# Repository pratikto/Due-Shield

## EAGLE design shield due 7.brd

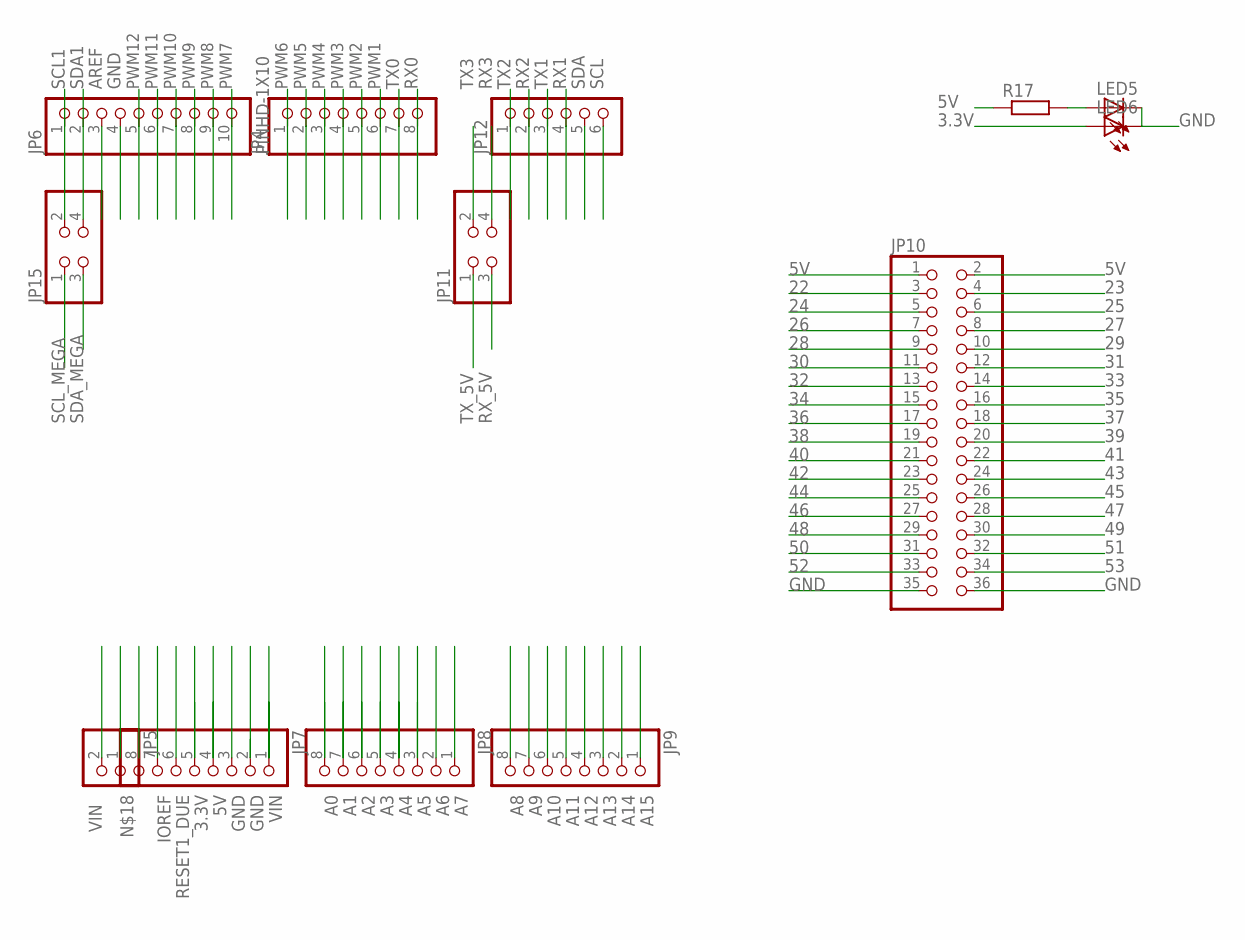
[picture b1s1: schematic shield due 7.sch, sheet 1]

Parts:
JP4, JP7: PINHD-1X8; 1X08
JP5: PINHD-1X2; 1X02
JP6: PINHD-1X10; 1X10-BIG
JP8, JP9: PINHD-1X8BIG; 1X08-BIG
JP10: PINHD-2X18; 2X18
JP11, JP15: PINHD-2X2; 2X02
JP12: PINHD-1X6; 1X06
LED5, LED6: LEDCHIPLED_0805; CHIPLED_0805
R17: R-EU_R0805W; R0805W

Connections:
3.3V: JP7.5, LED6.A; also elsewhere on the board
5V: JP7.4, JP10.1, JP10.2, R17.1; also elsewhere on the board
22: JP10.3
23: JP10.4
24: JP10.5
25: JP10.6
26: JP10.7
27: JP10.8
28: JP10.9
29: JP10.10
30: JP10.11
31: JP10.12
32: JP10.13
33: JP10.14
34: JP10.15
35: JP10.16; also elsewhere on the board
36: JP10.17; also elsewhere on the board
37: JP10.18; also elsewhere on the board
38: JP10.19; also elsewhere on the board
39: JP10.20; also elsewhere on the board
40: JP10.21; also elsewhere on the board
41: JP10.22
42: JP10.23
43: JP10.24
44: JP10.25
45: JP10.26
46: JP10.27
47: JP10.28
48: JP10.29
49: JP10.30
50: JP10.31
51: JP10.32
52: JP10.33
53: JP10.34
A0: JP8.8
A1: JP8.7
A2: JP8.6
A3: JP8.5
A4: JP8.4
A5: JP8.3
A6: JP8.2
A7: JP8.1
A8: JP9.8
A9: JP9.7
A10: JP9.6
A11: JP9.5
A12: JP9.4
A13: JP9.3
A14: JP9.2
A15: JP9.1
AREF: JP6.3
GND: JP6.4, JP7.2, JP7.3, JP10.35, JP10.36, LED5.C, LED6.C; also elsewhere on the board
IOREF: JP7.7
unnamed: LED5.A, R17.2
PWM1: JP4.6
PWM2: JP4.5
PWM3: JP4.4
PWM4: JP4.3
PWM5: JP4.2
PWM6: JP4.1
PWM7: JP6.10
PWM8: JP6.9
PWM9: JP6.8
PWM10: JP6.7
PWM11: JP6.6
PWM12: JP6.5
RESET1_DUE: JP7.6
RX0: JP4.8
RX1: JP12.4
RX2: JP12.2
RX3: JP11.4; also elsewhere on the board
RX_5V: JP11.3; also elsewhere on the board
SCL: JP12.6
SCL1: JP6.1, JP15.2; also elsewhere on the board
SCL_MEGA: JP15.1; also elsewhere on the board
SDA: JP12.5
SDA1: JP6.2, JP15.4; also elsewhere on the board
SDA_MEGA: JP15.3; also elsewhere on the board
TX0: JP4.7
TX1: JP12.3
TX2: JP12.1
TX3: JP11.2; also elsewhere on the board
TX_5V: JP11.1; also elsewhere on the board
VIN: JP5.2, JP7.1; also elsewhere on the board
VIN_BAT: JP5.1; also elsewhere on the board

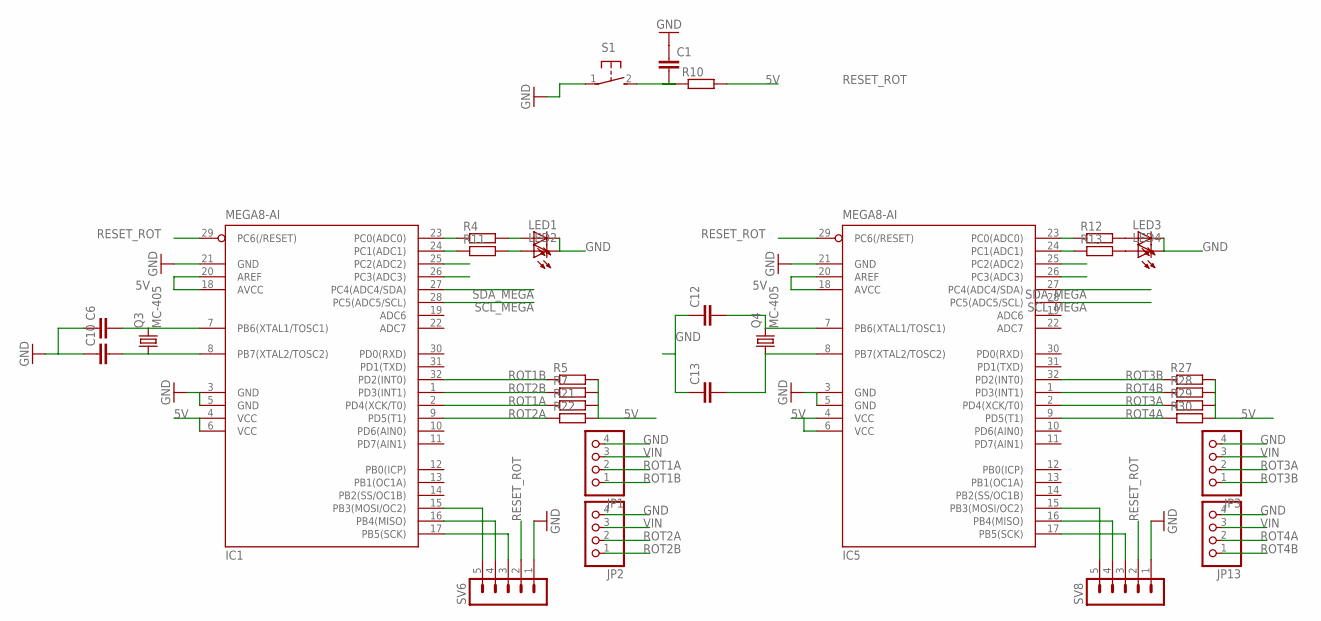
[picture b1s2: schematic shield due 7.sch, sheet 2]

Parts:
C1, C6, C10, C12, C13: C-EUC0805K; C0805K
IC1, IC5: MEGA8-AI; TQFP32-08; MPN ATMEGA8-16AU
JP1, JP2, JP3, JP13: PINHD-1X4; 1X04
LED1, LED2, LED3, LED4: LEDCHIPLED_0805; CHIPLED_0805
Q3, Q4: MC-405
R4, R5, R7, R10, R11, R12, R13, R21, R22, R27, R28, R29, R30: R-EU_R0805W; R0805W
S1: 31-XX; B3F-31XX
SV6, SV8: MA05-1

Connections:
5V: IC1.4 (VCC), IC1.6 (VCC), IC1.18 (AVCC), IC1.20 (AREF), IC5.4 (VCC), IC5.6 (VCC), IC5.18 (AVCC), IC5.20 (AREF), R5.2, R7.2, R10.2, R21.2, R22.2, R27.2, R28.2, R29.2, R30.2; also elsewhere on the board
GND: C1.1, C6.1, C10.1, C12.1, C13.1, IC1.3 (GND), IC1.5 (GND), IC1.21 (GND), IC5.3 (GND), IC5.5 (GND), IC5.21 (GND), JP1.4, JP2.4, JP3.4, JP13.4, LED1.C, LED2.C, LED3.C, LED4.C, S1.1, SV6.1, SV8.1; also elsewhere on the board
unnamed: C6.2, IC1.7 (PB6(XTAL1/TOSC1)), Q3.2
unnamed: C10.2, IC1.8 (PB7(XTAL2/TOSC2)), Q3.1
unnamed: LED3.A, R12.2
unnamed: LED4.A, R13.2
unnamed: LED1.A, R4.2
unnamed: LED2.A, R11.2
unnamed: IC5.23 (PC0(ADC0)), R12.1
unnamed: IC1.17 (PB5(SCK)), SV6.3
unnamed: IC5.24 (PC1(ADC1)), R13.1
unnamed: IC1.16 (PB4(MISO)), SV6.4
unnamed: IC1.15 (PB3(MOSI/OC2)), SV6.5
unnamed: C12.2, IC5.7 (PB6(XTAL1/TOSC1)), Q4.2
unnamed: C13.2, IC5.8 (PB7(XTAL2/TOSC2)), Q4.1
unnamed: IC1.23 (PC0(ADC0)), R4.1
unnamed: IC1.24 (PC1(ADC1)), R11.1
unnamed: IC5.17 (PB5(SCK)), SV8.3
unnamed: IC5.16 (PB4(MISO)), SV8.4
unnamed: IC5.15 (PB3(MOSI/OC2)), SV8.5
RESET_ROT: C1.2, IC1.29 (PC6(/RESET)), IC5.29 (PC6(/RESET)), R10.1, S1.2 (S), SV6.2, SV8.2
ROT1A: IC1.2 (PD4(XCK/T0)), JP1.2, R21.1
ROT1B: IC1.32 (PD2(INT0)), JP1.1, R5.1
ROT2A: IC1.9 (PD5(T1)), JP2.2, R22.1
ROT2B: IC1.1 (PD3(INT1)), JP2.1, R7.1
ROT3A: IC5.2 (PD4(XCK/T0)), JP3.2, R29.1
ROT3B: IC5.32 (PD2(INT0)), JP3.1, R27.1
ROT4A: IC5.9 (PD5(T1)), JP13.2, R30.1
ROT4B: IC5.1 (PD3(INT1)), JP13.1, R28.1
SCL_MEGA: IC1.28 (PC5(ADC5/SCL)), IC5.28 (PC5(ADC5/SCL)); also elsewhere on the board
SDA_MEGA: IC1.27 (PC4(ADC4/SDA)), IC5.27 (PC4(ADC4/SDA)); also elsewhere on the board
VIN: JP1.3, JP2.3, JP3.3, JP13.3; also elsewhere on the board

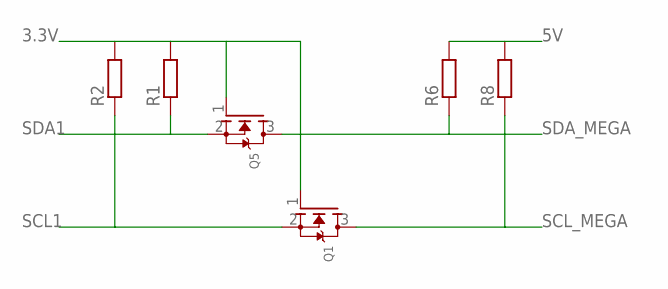
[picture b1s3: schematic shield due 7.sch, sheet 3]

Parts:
Q1, Q5: MOSFET-NWAVE; SOT23-W
R1, R2, R6, R8: R-EU_R0805W; R0805W

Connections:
3.3V: Q1.1 (G), Q5.1 (G), R1.2, R2.2; also elsewhere on the board
5V: R6.2, R8.2; also elsewhere on the board
SCL1: Q1.2 (S), R2.1; also elsewhere on the board
SCL_MEGA: Q1.3 (D), R8.1; also elsewhere on the board
SDA1: Q5.2 (S), R1.1; also elsewhere on the board
SDA_MEGA: Q5.3 (D), R6.1; also elsewhere on the board

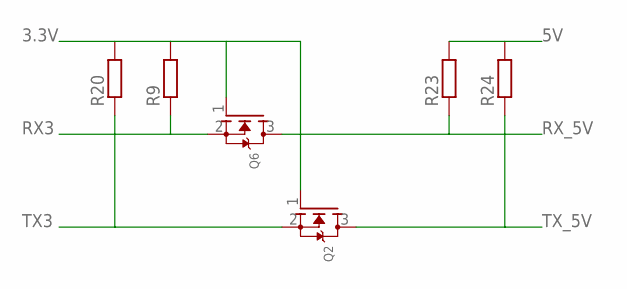
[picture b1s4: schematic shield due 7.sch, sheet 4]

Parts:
Q2, Q6: MOSFET-NWAVE; SOT23-W
R9, R20, R23, R24: R-EU_R0805W; R0805W

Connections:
3.3V: Q2.1 (G), Q6.1 (G), R9.2, R20.2; also elsewhere on the board
5V: R23.2, R24.2; also elsewhere on the board
RX3: Q6.2 (S), R9.1; also elsewhere on the board
RX_5V: Q6.3 (D), R23.1; also elsewhere on the board
TX3: Q2.2 (S), R20.1; also elsewhere on the board
TX_5V: Q2.3 (D), R24.1; also elsewhere on the board

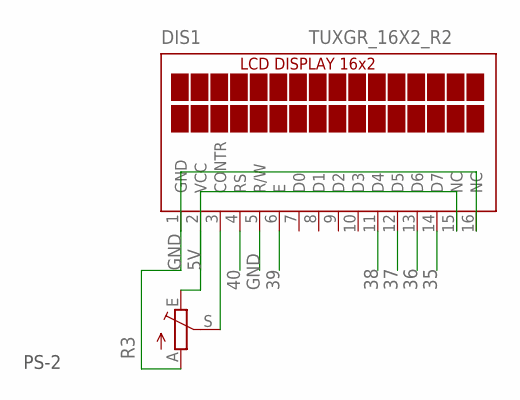
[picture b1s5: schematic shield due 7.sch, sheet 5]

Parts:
DIS1: TUXGR_16X2_R2
R3: TRIM_EU-CA6V; CA6V

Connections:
5V: DIS1.2 (VCC), DIS1.15 (NC), R3.E; also elsewhere on the board
35: DIS1.14 (D7); also elsewhere on the board
36: DIS1.13 (D6); also elsewhere on the board
37: DIS1.12 (D5); also elsewhere on the board
38: DIS1.11 (D4); also elsewhere on the board
39: DIS1.6 (E); also elsewhere on the board
40: DIS1.4 (RS); also elsewhere on the board
GND: DIS1.1 (GND), DIS1.5 (R/W), DIS1.16 (NC), R3.A; also elsewhere on the board
unnamed: DIS1.3 (CONTR), R3.S

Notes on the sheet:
PS-2

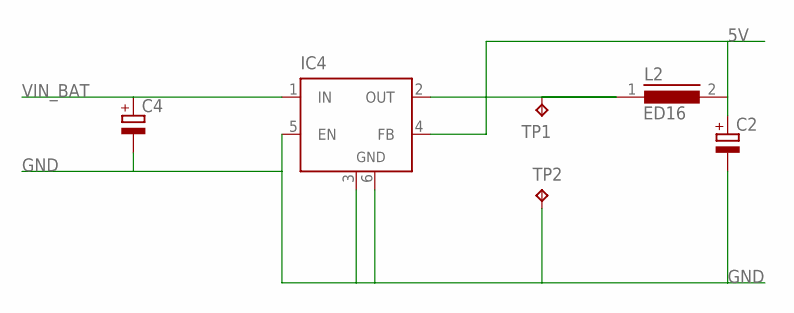
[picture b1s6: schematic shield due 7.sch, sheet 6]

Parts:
C2: CPOL-EU150CLZ-1010; 150CLZ-1010
C4: CPOL-EU153CLV-1014; 153CLV-1014
IC4: LM2596S; TO263-5
L2: ED16
TP1, TP2: TPPAD1-13; P1-13

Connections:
5V: C2.+, IC4.4 (FB), L2.2; also elsewhere on the board
A: IC4.2 (OUT), L2.1, TP1.TP
GND: C2.-, C4.-, IC4.3 (GND), IC4.5 (EN), IC4.6 (GND), TP2.TP; also elsewhere on the board
VIN_BAT: C4.+, IC4.1 (IN); also elsewhere on the board

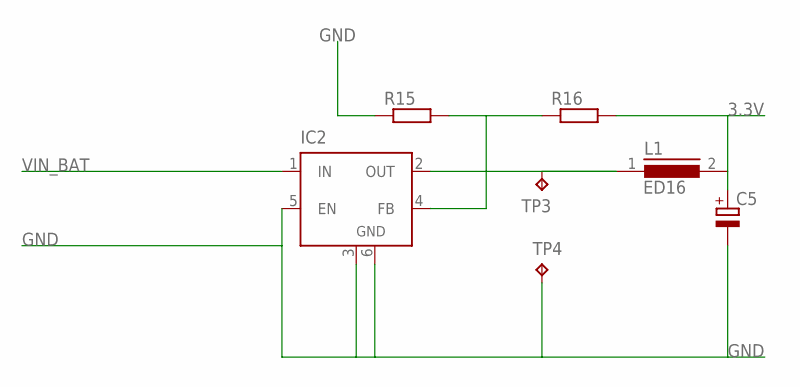
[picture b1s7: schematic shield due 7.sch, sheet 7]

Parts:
C5: CPOL-EU150CLZ-1010; 150CLZ-1010
IC2: LM2596S; TO263-5
L1: ED16
R15, R16: R-EU_R0805W; R0805W
TP3, TP4: TPPAD1-13; P1-13

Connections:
3.3V: C5.+, L1.2, R16.2; also elsewhere on the board
A16: IC2.2 (OUT), L1.1, TP3.TP
GND: C5.-, IC2.3 (GND), IC2.5 (EN), IC2.6 (GND), R15.1, TP4.TP; also elsewhere on the board
SADSA: IC2.4 (FB), R15.2, R16.1
VIN_BAT: IC2.1 (IN); also elsewhere on the board

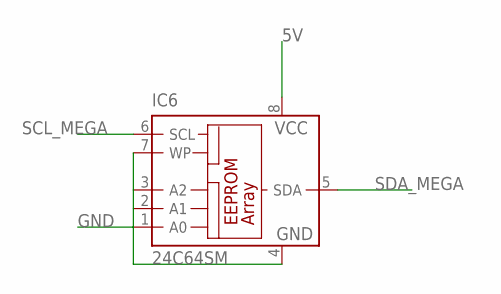
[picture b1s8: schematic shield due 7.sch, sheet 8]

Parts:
IC6: 24C64SM; SO-08M

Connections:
5V: IC6.8 (VCC); also elsewhere on the board
GND: IC6.1 (A0), IC6.2 (A1), IC6.3 (A2), IC6.4 (GND), IC6.7 (WP); also elsewhere on the board
SCL_MEGA: IC6.6 (SCL); also elsewhere on the board
SDA_MEGA: IC6.5 (SDA); also elsewhere on the board

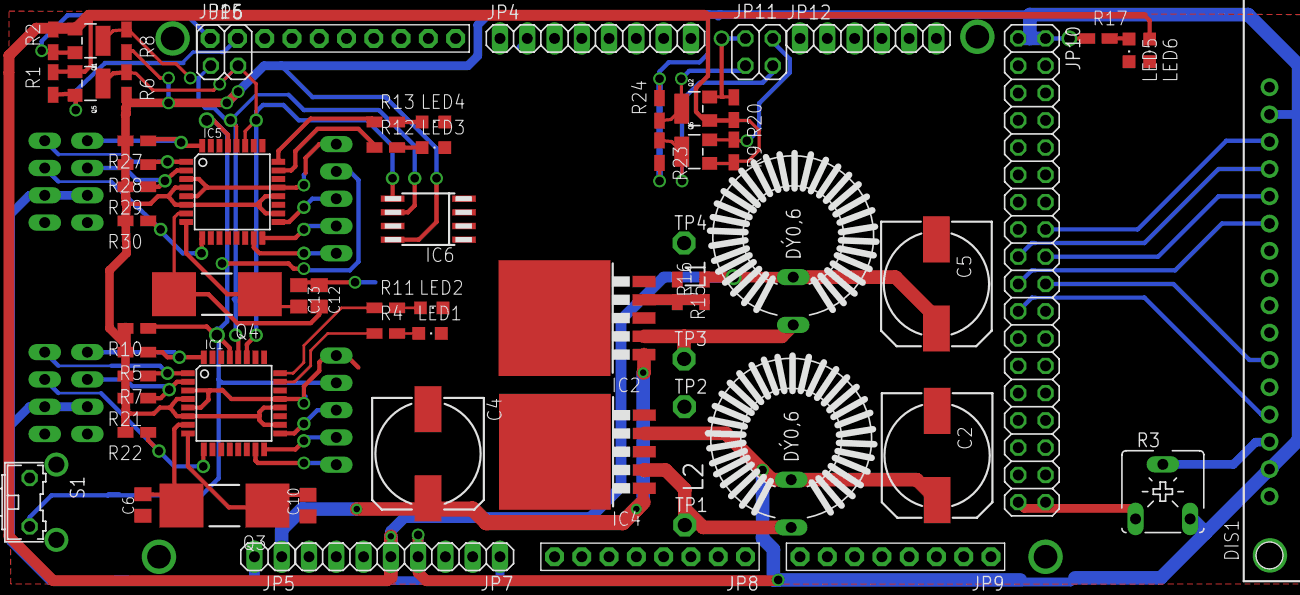
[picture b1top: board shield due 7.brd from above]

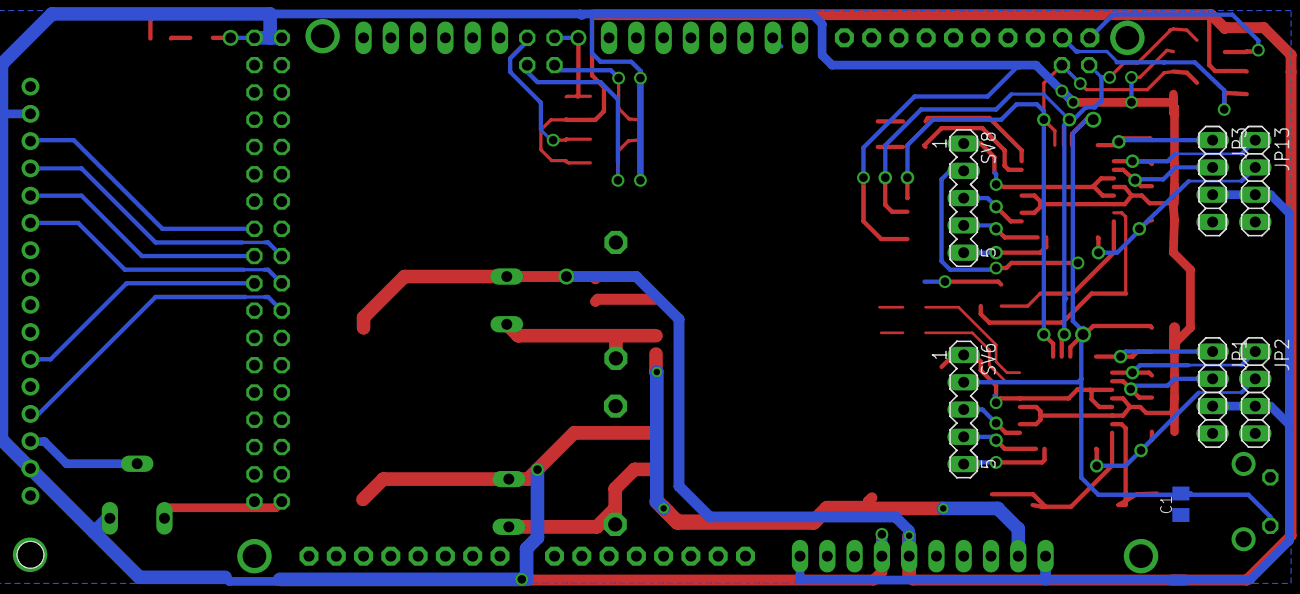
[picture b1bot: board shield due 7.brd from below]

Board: 2 copper layers, 74 parts (7 on the bottom side), 51 nets.
